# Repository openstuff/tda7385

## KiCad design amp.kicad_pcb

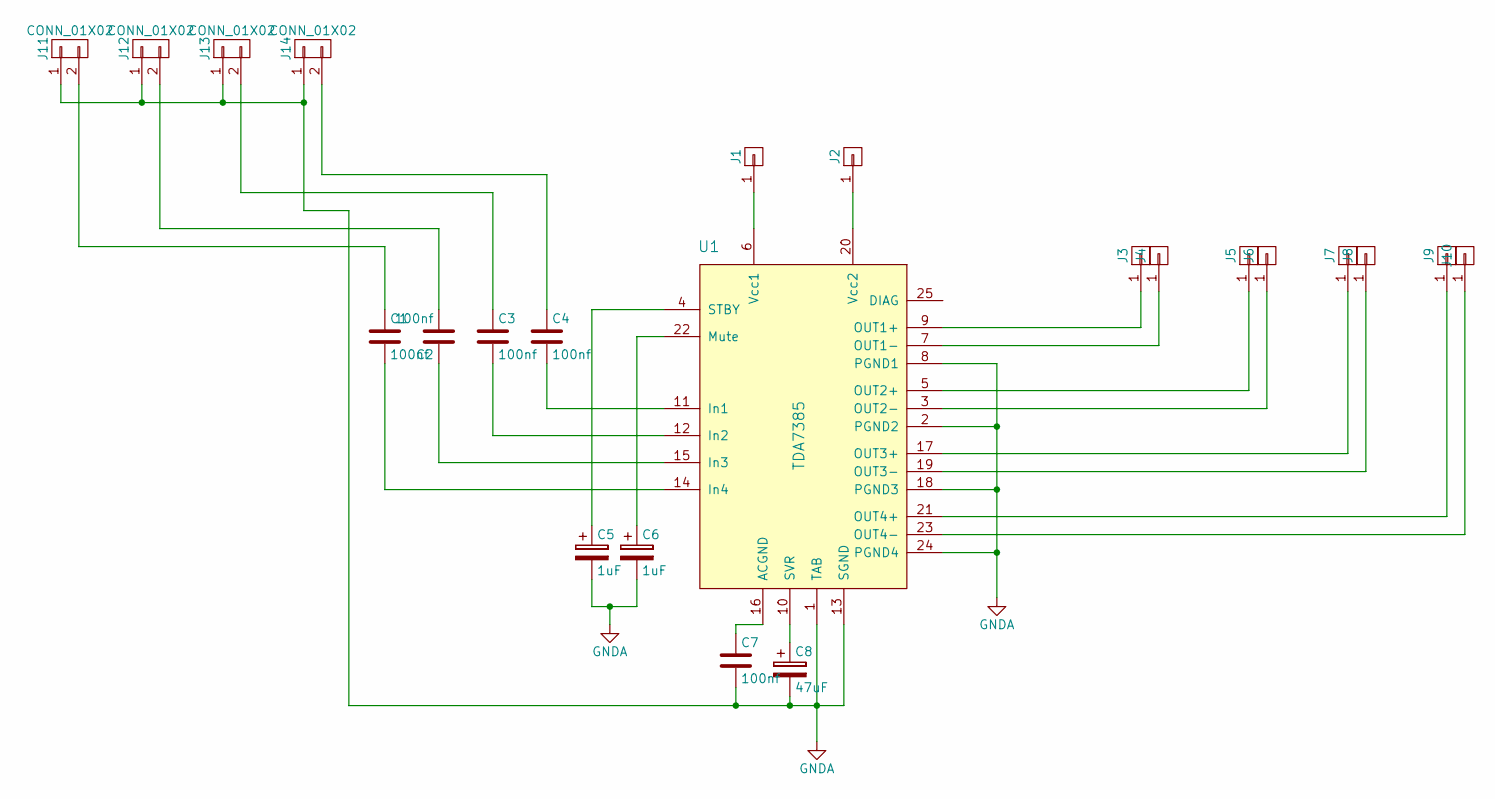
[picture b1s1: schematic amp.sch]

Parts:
C1, C2, C3, C4, C7: 100nf; C_Disc_D7.5mm_W2.5mm_P5.00mm
C5, C6: 1uF; CP_Radial_D5.0mm_P2.50mm
C8: 47uF; CP_Radial_D5.0mm_P2.50mm
J1, J2, J3, J4, J5, J6, J7, J8, J9, J10: CONN_01X01; PINTST
J11, J12, J13, J14: CONN_01X02; Pin_Header_Straight_1x02_Pitch2.54mm
U1: TDA7385; tda7385

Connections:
GNDA: C5.2, C6.2, C7.2, C8.2, J11.1, J12.1, J13.1, J14.1, U1.1 (TAB), U1.2 (PGND2), U1.8 (PGND1), U1.13 (SGND), U1.18 (PGND3), U1.24 (PGND4)
unnamed: C1.1, J11.2
unnamed: C1.2, U1.14 (In4)
unnamed: C2.1, U1.15 (In3)
unnamed: C2.2, J12.2
unnamed: C3.1, J13.2
unnamed: C3.2, U1.12 (In2)
unnamed: C4.1, J14.2
unnamed: C4.2, U1.11 (In1)
unnamed: C5.1, U1.4 (STBY)
unnamed: C6.1, U1.22 (Mute)
unnamed: C7.1, U1.16 (ACGND)
unnamed: C8.1, U1.10 (SVR)
unnamed: J1.1, U1.6 (Vcc1)
unnamed: J2.1, U1.20 (Vcc2)
unnamed: J3.1, U1.9 (OUT1+)
unnamed: J4.1, U1.7 (OUT1-)
unnamed: J5.1, U1.5 (OUT2+)
unnamed: J6.1, U1.3 (OUT2-)
unnamed: J7.1, U1.17 (OUT3+)
unnamed: J8.1, U1.19 (OUT3-)
unnamed: J9.1, U1.21 (OUT4+)
unnamed: J10.1, U1.23 (OUT4-)

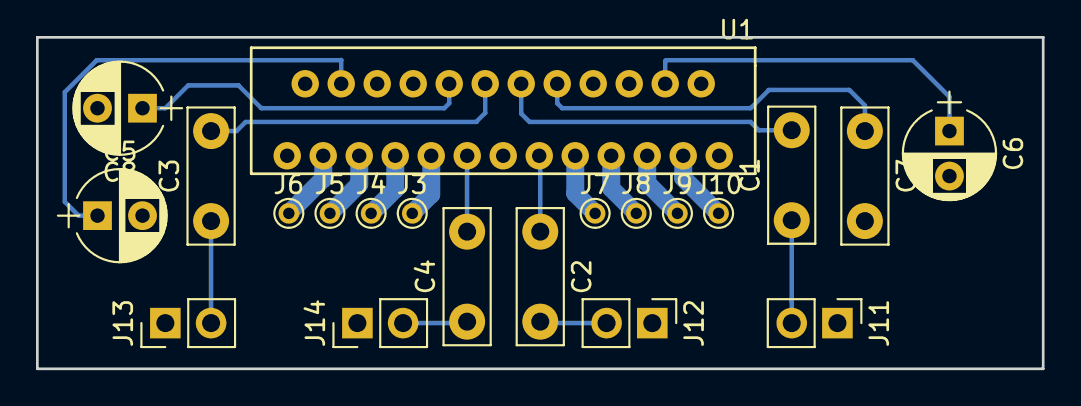
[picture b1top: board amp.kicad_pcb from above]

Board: 2 copper layers, 55.9 x 18.4 mm, 21 parts (0 on the bottom side), 21 nets.

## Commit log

2017-04-11 step2
2017-04-12 final pcb for amp board
2017-04-12 start work on pwrsupply
